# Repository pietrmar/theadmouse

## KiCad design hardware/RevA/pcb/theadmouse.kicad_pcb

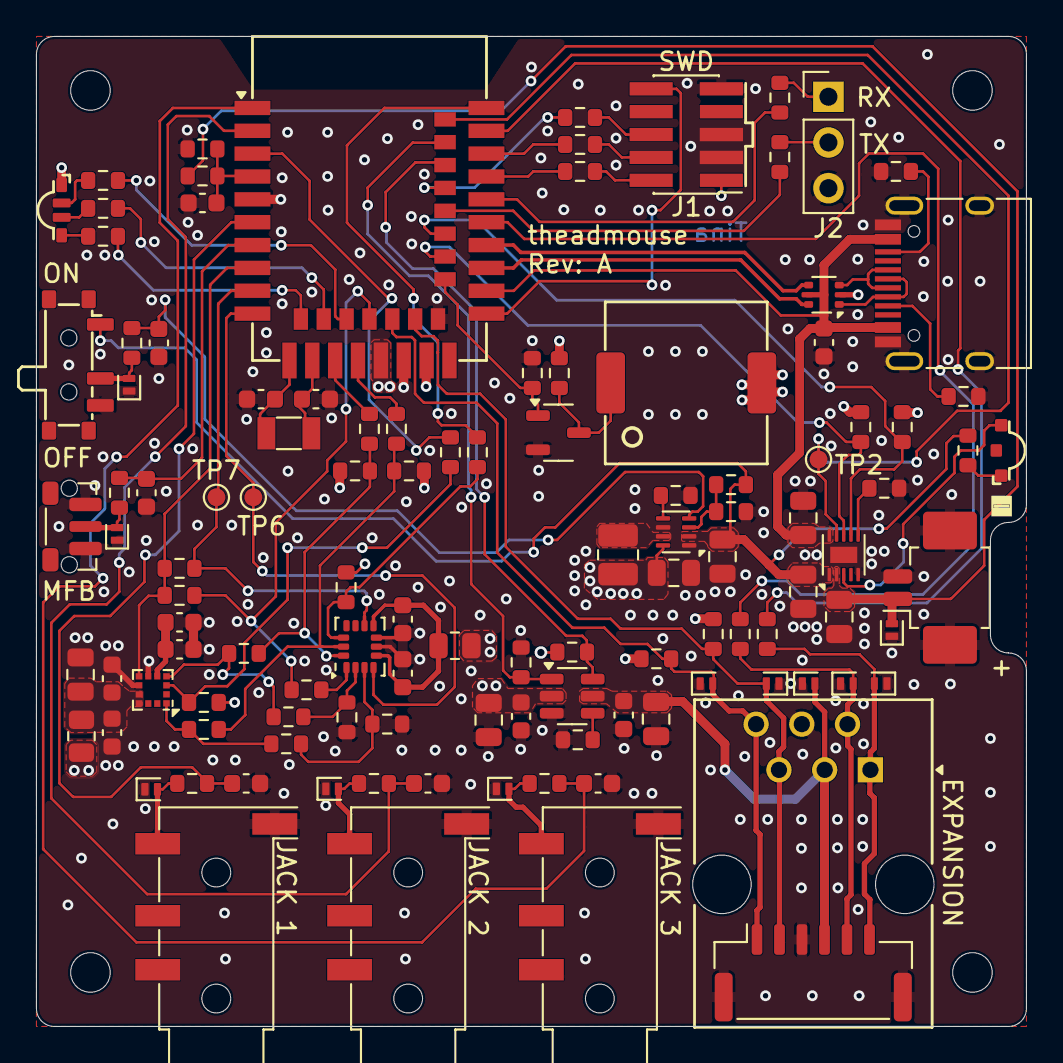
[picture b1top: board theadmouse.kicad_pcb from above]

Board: 4 copper layers, 55.0 x 55.0 mm, 119 parts (0 on the bottom side), 82 nets.

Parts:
C1, C2: 15p; C_0603_1608Metric
C3, C8, C11, C13, C14, C15, C16, C17, C19, C26: 100n; C_0603_1608Metric
C4, C5, C6, C9, C10, C12, C18, C25: 10u; C_0805_2012Metric
C7, C21, C22, C23, C24: 10n; C_0603_1608Metric
D1, D2, D3, D4, D5, D6, D7, D8, D9, D10, D12: H5VL10B; D_SOD-882
D11: LED_STATUS; LED_RGB_TUOZHAN_P4-1204RGBWS2-1.5T-A_Horizontal
D13: LED_PGOOD; LED_Green_MEIHUA_MHS110UGCT_Horizontal
H1, H2, H3, H4: MountingHole; MountingHole_2.2mm_M2_ISO7380
J1: CON_SWD; PinHeader_2x05_P1.27mm_Vertical_SMD
J2: CON_UART; PinHeader_1x03_P2.54mm_Vertical
J4: TYPE-C-31-M-12; USB_C_Receptacle_HRO_TYPE-C-31-M-12_Custom3D
J5: CON_BAT; Molex_PicoBlade_53261-0271_1x02-1MP_P1.25mm_Horizontal
J6: CON_EXT; JST_GH_SM06B-GHS-TB_1x06-1MP_P1.25mm_Horizontal
J7: CON_EXT_RJ; RJ25_TE_215876-1_Horizontal
J8, J9, J10: PJ-320D-4A; Jack_3.5mm_KoreanHropartsElec_PJ-320D-4A_Horizontal_Custom
L1: 2u2; L_1008_2520Metric
LS1: FUET-9018; Buzzer_FUET_FST-9018_9x9mm
Q1: HL2312; SOT-23-3
R1, R2, R3, R4, R5, R6, R21, R30: 10k; R_0603_1608Metric
R7, R8, R11, R12, R41, R44, R45, R49: 100R; R_0603_1608Metric
R9, R10, R13, R14, R16, R17, R18, R53: 22R; R_0603_1608Metric
R19, R20: 5k1; R_0603_1608Metric
R22: 4M02; R_0603_1608Metric
R23: 10M; R_0603_1608Metric
R24, R26, R32, R34, R35, R36, R37, R38, R39, R40: 0R; R_0603_1608Metric
R25, R43: 100k; R_0603_1608Metric
R27: 4k3; R_0603_1608Metric
R28: 267k; R_0603_1608Metric
R29, R50, R51: 470k; R_0603_1608Metric
R31, R33: 0R; R_0805_2012Metric
R42: 1k; R_0603_1608Metric
R46: 470R; R_0603_1608Metric
R47: 390R; R_0603_1608Metric
R48: 270R; R_0603_1608Metric
R52: 1k5; R_0603_1608Metric
SW1: SW_PWR; SW_SPDT_ALPS_SSSS811101_SMT_Horizontal
SW2: SW_MFB; SW_Push_1P1T-MP_NO_Horizontal_Alps_SKRTLAE010_Custom3D
TP2: ~{CHRG_INT}; TestPoint_Pad_D1.0mm
TP6: SENS_IMU_INT1; TestPoint_Pad_D1.0mm
TP7: SENS_IMU_INT2; TestPoint_Pad_D1.0mm
U1: E73-2G4M08S1C; Module_RF_Ebyte_E73-2G4M08S1C_Castellated
U2: USBLC6-2P6; SOT-666
U3: BQ25186; Texas_DLH0010A_WSON-10-1EP_2.2x2mm_P0.4mm_EP0.9x1.5mm
U4: TPS22950; SOT-23-6
U5: TPS62840DLC; Texas_VSON-HR-8_1.5x2mm_P0.5mm
U6: LSM6DSL; LGA-14_3x2.5mm_P0.5mm_LayoutBorder3x4y
U7: LIS2MDL; LGA-12_2x2mm_P0.5mm
Y1: 32.768 kHz; Crystal_SMD_3215-2Pin_3.2x1.5mm

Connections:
/BTN_JACK_1: C21.2, R41.1, U1.6 (P1.13)
/BTN_JACK_2: C22.2, R44.1, U1.2 (P1.10)
/BTN_JACK_3: C23.2, R45.1, U1.1 (P1.11)
/BTN_MFB: C24.2, R49.1, U1.7 (P0.02/AIN0)
/CHRG_I2C_SCL: R1.2, U1.30 (P0.17), U3.8 (SCL)
/CHRG_I2C_SDA: R2.2, U1.32 (P0.20), U3.7 (SDA)
/EXT_3V3_EN: R29.1, U1.40 (P1.04), U4.1 (ON)
/EXT_GPIO_1: D4.2 (A2), J6.5 (Pin_2), J7.2, R11.2
/EXT_GPIO_2: D3.2 (A2), J6.6 (Pin_1), J7.1, R12.1
/EXT_I2C_SCL: D7.2 (A2), J6.1 (Pin_6), J7.6, R5.2, U1.20 (P0.12)
/EXT_I2C_SDA: D6.2 (A2), J6.2 (Pin_5), J7.5, R6.2, U1.22 (P0.07)
/LED_B: R48.2, U1.16 (P0.08)
/LED_G: R47.2, U1.14 (P0.06)
/LED_R: R46.2, U1.12 (P0.26)
/Power/~CHRG_PG: D13.1 (K), U3.3 (~PG/GPO)
/SENS_IMU_INT_1: TP6.1, U1.10 (P0.30/AIN6), U6.4 (INT1)
/SENS_IMU_INT_2: R32.2, TP7.1, U1.9 (P0.31/AIN7), U6.9 (INT2)
/SENS_MAG_DRDY: R32.1, R40.2, U1.8 (P0.29/AIN5), U7.7 (DRDY)
/SENS_SPI_MISO: R40.1, R53.2, U1.18 (P0.04/AIN2)
/SENS_SPI_MOSI: R4.2, R13.1, R39.2, U6.14 (SDA)
/SENS_SPI_SCLK: R3.2, R14.1, R38.2, U6.13 (SCL)
/SPK_PWM: Q1.1 (G), R43.2, U1.28 (P0.15)
/SWCLK: J1.4, R10.2
/SWDIO: J1.2, R9.1
/SWO: J1.6, R16.2
/UART_RX: J2.1, R8.1
/UART_TX: J2.2, R7.2
/USB_D+: U1.31 (DP), U2.4 (I/O2)
/USB_D-: U1.29 (DM), U2.6 (I/O1)
/VBAT_MEAS: C7.1, R22.2, R23.1, U1.4 (P0.28/AIN4)
/~CHRG_INT: TP2.1, U1.42 (P1.06), U3.9 (~INT)
/~EXT_3V3_FAULT: R25.2, U1.38 (P1.02), U4.6 (~FLT)
/~RESET: J1.10, U1.26 (P0.18/RESET)
/~SENS_IMU_CS: R17.1, R50.2, U6.12 (CS)
/~SENS_MAG_CS: R18.2, R51.2, U7.3 (~CS)
EXT_3V3: C8.1, C9.1, D5.2 (A2), J6.4 (Pin_3), J7.3, U4.5 (VOUT)
GND: C1.2, C2.2, C3.2, C4.2, C5.2, C6.2, C7.2, C8.2, C9.2, C10.2, C11.2, C12.2, C13.2, C14.2, C15.2, C16.2, C17.2, C18.2, C19.2, C21.1, C22.1, C23.1, C24.1, C25.2, C26.2, D1.1 (A1), D2.1 (A1), D3.1 (A1), D4.1 (A1), D5.1 (A1), D6.1 (A1), D7.1 (A1), D8.1 (A1), D9.1 (A1), D10.1 (A1), D12.1 (A1), J1.3, J1.5, J1.9, J2.3, J4.A1 (GND), J4.A12 (GND), J4.B1 (GND), J4.B12 (GND), J4.S1 (SHIELD), J5.2, J5.MP (MountPin), J6.3 (Pin_4), J6.MP (MountPin), J7.4, J8.G, J9.G, J10.G, Q1.2 (S), R19.2, R20.2, R21.1, R23.2, R26.1, R27.2, R28.1, R29.2, R36.1, R37.2, R43.1, SW1.3 (A), SW2.1, U1.5 (GND@1), U1.21 (GND@2), U1.24 (GND@3), U2.2 (GND), U3.5 (GND), U3.11 (THERMAL), U4.3 (GND), U5.1 (GND), U5.6 (STOP), U6.6 (GND), U6.7 (GND), U7.6 (GND), U7.8 (GND)
unnamed: D2.2 (A2), R30.1, SW1.2 (B)
unnamed: D8.2 (A2), J8.T, R41.2
unnamed: D9.2 (A2), J9.T, R44.2
unnamed: D10.2 (A2), J10.T, R45.2
unnamed: D11.2 (BK), R48.1
unnamed: D11.1 (GK), R47.1
unnamed: D11.3 (RK), R46.1
unnamed: D12.2 (A2), R49.2, SW2.2
unnamed: D13.2 (A), R52.1
unnamed: J4.A5 (CC1), R20.1
unnamed: J4.B5 (CC2), R19.1
unnamed: J4.A6 (D+), J4.B6 (D+), U2.3 (I/O2)
unnamed: J4.A7 (D-), J4.B7 (D-), U2.1 (I/O1)
unnamed: LS1.2, Q1.3 (D), R42.1
unnamed: R10.1, U1.39 (SWDCLK)
unnamed: R9.2, U1.37 (SWDIO)
unnamed: C1.1, U1.11 (P0.00/XL1), Y1.2
unnamed: C2.1, U1.13 (P0.01/XL2), Y1.1
unnamed: R18.1, U1.3 (P0.03/AIN1)
unnamed: R13.2, U1.15 (P0.05/AIN3)
unnamed: R12.2, U1.41 (P0.09/NFC1)
unnamed: R17.2, U1.43 (P0.10/NFC2)
unnamed: R11.1, U1.33 (P0.13)
unnamed: R7.1, U1.34 (P0.22)
unnamed: R8.2, U1.35 (P0.24)
unnamed: R16.1, U1.36 (P1.00)
unnamed: R14.2, U1.17 (P1.09)
unnamed: R21.2, U3.6 (TS/MR)
unnamed: R27.1, U4.4 (ILIM)
unnamed: C13.1, R30.2, U5.4 (EN)
unnamed: R24.1, R26.2, U5.3 (MODE)
unnamed: L1.1, U5.7 (SW)
unnamed: R28.2, U5.5 (VSET)
unnamed: R35.1, R36.2, U6.3 (SCX)
unnamed: R53.1, U6.1 (SDO/SA0)
unnamed: R34.2, R37.1, U6.2 (SDX)
unnamed: C14.1, C15.1, R31.1, U6.5 (VDDIO), U6.8 (VDD)
unnamed: C19.1, C26.1, U7.5 (C1)
unnamed: R35.2, R38.1, U7.1 (SCL/SPC)
unnamed: R34.1, R39.1, U7.4 (SDA/SDI/SDO)
unnamed: C16.1, C17.1, C18.1, R33.1, U7.9 (Vdd), U7.10 (Vdd_IO)
VBAT: C6.1, D1.2 (A2), J5.1, R22.1, U3.2 (BAT)
VBUS: C3.1, C4.1, J4.A4 (VBUS), J4.A9 (VBUS), J4.B4 (VBUS), J4.B9 (VBUS), U1.27 (VBUS), U2.5 (VBUS), U3.10 (IN)
VDD_3V3: C10.1, C11.1, C25.1, D11.4 (A), J1.1, L1.2, LS1.1, R1.1, R2.1, R3.1, R4.1, R5.1, R6.1, R25.1, R31.2, R33.2, R42.2, R50.1, R51.1, U1.19 (VDD), U1.23 (VDDH), U4.2 (VIN), U5.8 (VOS)
VSYS: C5.1, C12.1, R24.2, R52.2, SW1.1 (C), U3.1 (SYS), U5.2 (VIN)

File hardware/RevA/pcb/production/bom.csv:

Designator,Footprint,Quantity,Value,LCSC Part #
"C1, C2",0603,2,15p,C1644
"C10, C12, C18, C25, C4, C5, C6, C9",0805,8,10u,C15850
"C11, C13, C14, C15, C16, C17, C19, C26, C3, C8",0603,10,100n,C2762593
"C21, C22, C23, C24, C7",0603,5,10n,C85973
"D1, D10, D12, D2, D3, D4, D5, D6, D7, D8, D9",D_SOD-882,11,H5VL10B,C7420372
D11,LED_RGB_TUOZHAN_P4-1204RGBWS2-1.5T-A_Horizontal,1,LED_STATUS,C2827295
D13,LED_Green_MEIHUA_MHS110UGCT_Horizontal,1,LED_PGOOD,C404269
J1,PinHeader_2x05_P1.27mm_Vertical_SMD,1,CON_SWD,C41376037
"J10, J8, J9",Jack_3.5mm_KoreanHropartsElec_PJ-320D-4A_Horizontal_Custom,3,PJ-320D-4A,C95562
J4,USB_C_Receptacle_HRO_TYPE-C-31-M-12_Custom3D,1,TYPE-C-31-M-12,C165948
J5,Molex_PicoBlade_53261-0271_1x02-1MP_P1.25mm_Horizontal,1,CON_BAT,C177225
J6,JST_GH_SM06B-GHS-TB_1x06-1MP_P1.25mm_Horizontal,1,CON_EXT,C133065
L1,1008,1,2u2,C2043106
LS1,Buzzer_FUET_FST-9018_9x9mm,1,FUET-9018,C391035
Q1,SOT-23-3,1,HL2312,C28646272
"R1, R2, R21, R30, R5, R6",0603,6,10k,
"R10, R13, R14, R16, R17, R18, R53, R9",0603,8,22R,
"R11, R12, R41, R44, R45, R49, R7, R8",0603,8,100R,
"R19, R20",0603,2,5k1,
R22,0603,1,4M02,C322160
R23,0603,1,10M,
"R25, R43",0603,2,100k,
"R26, R36, R37, R38, R39",0603,5,0R,
R27,0603,1,4k3,
R28,0603,1,267k,
"R31, R33",0805,2,0R,
R42,0603,1,1k,
R46,0603,1,470R,
R47,0603,1,390R,
R48,0603,1,270R,
"R50, R51",0603,2,470k,
R52,0603,1,1k5,
SW1,SW_SPDT_ALPS_SSSS811101_SMT_Horizontal,1,SW_PWR,C109335
SW2,SW_Push_1P1T-MP_NO_Horizontal_Alps_SKRTLAE010_Custom3D,1,SW_MFB,C110293
U1,Module_RF_Ebyte_E73-2G4M08S1C_Castellated,1,E73-2G4M08S1C,C356849
U2,SOT-666,1,USBLC6-2P6,C15999
U3,Texas_DLH0010A_WSON-10-1EP_2.2x2mm_P0.4mm_EP0.9x1.5mm,1,BQ25186,C44639442
U4,SOT-23-6,1,TPS22950,C7587833
U5,Texas_VSON-HR-8_1.5x2mm_P0.5mm,1,TPS62840DLC,C2071859
U6,LGA-14_3x2.5mm_P0.5mm_LayoutBorder3x4y,1,LSM6DSL,C126672
U7,LGA-12_2x2mm_P0.5mm,1,LIS2MDL,C919695
Y1,Crystal_SMD_3215-2Pin_3.2x1.5mm,1,32.768 kHz,C32346

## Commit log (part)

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2025-02-27 initial commit of firmware directory
2025-02-27 firmware: basic logging setup
2025-03-22 firmware: empty app.overlay and slim down prj.conf for usage with the xiao_ble/nrf52840/sense
    The "xiao_ble/nrf52840/sense" already should have everything configured
    correctly for us.
2025-04-12 firmware: main.c: add `dfureboot` command
2025-04-13 firmware: first simple HID over GATT (HOG) support
    This is mostly based on the example provided by Zephyr.
2025-04-13 firmware: hog.c: use static GATT service definition again
2025-04-13 firmware: prj.conf: remove support for dynamic GATT service configuration
2025-04-13 firmware: main.c: read sensor data and pass send it out over HOG
2025-04-15 firmware: drivers: add custom lsm6dsl driver from the v3.7.99-ncs2 source tree
2025-04-15 firmware: drivers: lsm6dsl: set custom thread name on own trigger thread
2025-05-06 firmware: main.c: first proof of concept
2025-06-29 firmware: main.c: add comment
2025-08-09 hardware: RevA: create production output for JLCPCB
    These files were used to place the RevA order at JLCPCB.
2025-08-12 firmware: main.c: generate a friendly device name from the unique device ID
2025-08-14 firmware: add boilerplate code for the theadmouse board
2025-08-21 firmware: boards: theadmouse: initial board bringup
    Configures the following:
    - PWM for the RGB LED and the piezo buzzer
    - SPI in 4-wire mode (needs R40 stuffed on RevA)
    - LSM6DSL IMU
    - LIS2MDL Magnetometer
    - UART
2025-08-21 firmware: remove custom lsm6dsl driver for now
    I will take a detailed look at this later, but for now the demo is working
    with the driver from Zephyr unmodified.
2025-09-22 scripts: debug.sh: add `--enable-tpwr` flag
2025-10-15 firmware: boards: theadmouse: enable LIS2MDL runtime ODR setting
2025-10-16 firmware: main.c: first implementation of reading the magnetometer
    Just for a quick test, however it does not work fully yet.
2025-10-16 firmware: prj.conf: add CONFIG_UART_LINE_CTRL=y
2025-10-24 firmware: main.c: add telemetry first basic output for debugging
2025-10-24 WIP: firmware: theadmouse: implement forwarding beacons as HID packets
    This is very ugly and only a quick proof of concept, but it works, although
    pretty rough and low update rate.
2025-10-29 WIP: firmware: puckjs: implement periodic advertising
2025-10-29 WIP: firmware: theadmouse: parse target BT address from string
2025-11-03 firmware: boards: theadmouse: configure 0x1209:0x7EAD VID:PID for USB
    The VID and PID pair was requested from pid.codes in the following
    (currently pending) pull request:
    - https://github.com/pidcodes/pidcodes.github.com/pull/1112
2025-11-06 firmware: telemetry_uart: make the write call serialized
    This will prevent interleaved output in case there are multiple writers and
    the ringbuffer became full so that only a partial write was done.
2025-11-06 firmware: boards: theadmouse: set `mpi-cmd-uart` chosen node
2025-11-07 firmware: change USB device product name to TheadMouse
2025-11-07 firmware: at_cmd: add new `at_dispatch_cmd()` helper
    This will allow us to trigger commands without needing to go through the
    parsing step.
2025-11-07 firmware: at_cmd: make necessary types and helpers public needed for `at_dispatch_cmd()`
2025-11-07 firmware: at_cmd: first basic implementation of MX/MY commands
    For a quick proof of concept we can just use `hog_push_report()` directly
    but we will need a proper queueing system in place later.
2025-11-08 firmware: cmd_uart: don't pass len to `at_handle_line()` and use `AT_LINE_MAX` macro
2025-11-08 firmware: boards: theadmouse: add the GPIO buttons
2025-11-08 firmware: add button_manager
    This just takes button presses (or later other inputs) and dispatches AT
    commands from a table. Simple but works.
    The buttons can be defined in the device-tree.
2025-11-08 firmware: prj.conf: enable the input subsystem and the GPIO input key driver
2025-11-08 firmware: at_cmd: add first basic implementation of `AT BM <button>`
    These should be implemented cleaner, see the comments that were added.
2025-11-11 firmware: prj.conf: enable LittleFS filesystem
2025-11-12 firmware: at_cmd: reworkt the API a bit
    - Separate the parsing step into a `at_parse_line_[inplace|copy]()` function
    - Provide `*_inplace()` and `*_copy()` variants for parsing and handling
    - Add flags for parsing, for exampel to allow executing commands without the
    AT prefix
2025-11-12 firmware: main: disable `wipenvs` command for now
2025-11-13 firmware: at_cmd: minor log message change about "param type"
2025-11-13 firmware: button_manager: add new functions
    - Fix parameters in `button_manager_set_mapping()`
    - Add `button_manager_get_mapping()`
    - Add `button_manager_get_num_buttons()`
2025-11-13 firmware: main: call `slot_manager_init()`
2025-11-13 firmware: at_cmd: add TODO comment about possibly interleaving AT print functions
2025-11-13 firmware: at_cmd: make `at_param_get_str()` parameters const
2025-11-13 firmware: at_cmd: implement slot management commands and color command
2025-11-15 firmware: button_manager: add TODO comment about using callbacks
2025-11-15 firmware: button_manager: use new AT command queue
2025-11-17 firmware: at_cmd: make sure commands are dispatched only from the AT command thread
2025-11-17 firmware: slot_manager: load slot 0 by enqueueing it on the AT command queue
    This will ensure that the initial slot loading happens from the correct
    thread.
2025-11-18 firmware: at_cmd: implement `at_cmd_enqueue_and_wait_*()` functions
    Currently we only support K_FOREVER for the timeout for now, otherwise
    we would need to slab allocate the `result_ptr` and `done_sem` and use
    some reference counting.
2025-11-18 firmware: main: wait for AT command to finish and print error code
2025-11-18 firmware: slot_manager: drop `cmd == NULL` check
2025-11-19 firmware: add `input_protocol.h` header
    This will be mostly used to have hold common defines from the FABI/FLipMouse
    ecosystem.
    For now we only have the input mode.
2025-11-19 firmware: cmd_uart: remove mutex for `cmd_uart_write()`
    This is not needed, the caller to `cmd_uart_write()` should ensure that
    no concurrent writes happen otherwise the output will be interleaved.
2025-11-19 firmware: cmd_uart: add TODO comment about better receive line handling
2025-11-19 firmware: add headmouse_input module
    This creates two virtual input devices that can be used to push events
    which then will be sent using HID over GATT.
2025-11-19 firmware: at_cmd: MM: use `hm_input_report_rel()` now
    This will now correctly push the event into the input device, so we can
    handle it properly.
2025-11-19 firmware: remove IMU/MAG related things for now
    We will do this later correctly after we cleanly implemented HID over GATT
    and such.
2025-11-19 firmware: main: fix deprecation warning for `BT_LE_ADV_CONN`
2025-11-19 firmware: prj.conf: enable CONFIG_BT_HIDS
2025-11-25 firmware: main: sort includes and add TODO about BLE use-cases
2025-11-25 firmware: main: re-start advertising when disconnected
2025-11-26 firmware: prj.conf: use custom LSM6DSL driver
2025-11-29 firmware: prj.conf: use custom LIS2MDL driver
2025-12-02 firmware: re-add MadgwickAHRS library for now
    Downloaded from:
    https://x-io.co.uk/downloads/madgwick_algorithm_c.zip
2025-12-02 firmware: boards: theadmouse: use lis2mdl for `mpi,mag` chosen node
2025-12-02 firmware: prj.conf: enable LSM6DSL temperature readout
2025-12-03 firmware: telemetry_uart: make `telemetry_uart_write()` non-static
2026-01-14 firmware: at_cmd: clamp WA command at 1000 ms and print a warning
2026-01-20 firmware: button_manager: add `button_manager_get_button_state_string()` function
    This reports the current state of all buttons as a string of 1 and 0.
2026-01-20 firmware: at_cmd: include button states in periodic reporting
2026-01-20 firmware: at_cmd_param: change at_cmd_param_[clone|free]() API
    This changes the behavior assuming that the caller has already allocated
    the struct and this only handles the "deep" copy aspect, which currently
    is the case for a heap allocated string.
2026-01-21 firmware: at_cmd: make use of the new common `enum axis` enum
2026-01-21 firmware: at_cmd: include the absolute HID position in the report
2026-01-21 firmware: slot_manager: serialize sensitivity as AX, AY commands on save
2026-01-21 firmware: hm_hid_evt: use Zephyr USB HID header for HID_KEY_* codes
2026-01-21 firmware: at_cmd: format the `at_cmds[]` table consistently
2026-01-21 firmware: keymaps: adjust to our codebase and include in the build
2026-01-21 firmware: at_cmd: add KL command to get/set the keyboard layout
2026-01-21 firmware: at_cmd: more consistent error message for the KL command
2026-01-22 firmware: at_cmd: ID: report ForceSensor=IMU
2026-01-22 firmware: slot_manager: remove old input mode setting as it was moved to the motion_engine
2026-01-22 firmware: common.h: use explicit values for AXIS_X and AXIS_Y
2026-01-23 firmware: at_cmd_param: make the param flags into an enum
2026-01-23 firmware: main: use the new `AT_PARSER_FLAG_ALLOW_NO_PREFIX` flag
2026-01-23 firmware: slot_manager: serialize DX, DY values on save
2026-01-23 firmware: headmouse_input: add functions for handling KEY_* and KEYPAD_* strings
    The KEY_*/KEYPAD_* string key-codes are stored in an internal/intermediate
    code as a single uint8_t.
    Codes that are just ASCII characters will be mapped their own ASCII
    character. This allows us to make keyboard layout look-ups.
    Modifier keys are mapped into the ASCII range 0x10 - 0x17 which contains
    some unused ASCII control characters.
2026-01-23 firmware: at_cmd: add parsing and serializing of AT_CMD_PARAM_TYPE_KEYS
    Also print the partial string on error for better debugging purposes.
2026-01-23 firmware: at_cmd: add a new flag AT_CMD_FLAG_HOLD
    When this flag is set it is possible to pass an AT command code in the
    ctx that will be enqueue (with the same parameters) by the button manager
    when the button is released.
    This is not the cleanest architecture, but for now it'll do.
2026-01-23 firmware: button_manager: add input key-codes for UP, DOWN, LEFT and RIGHT
2026-01-24 firmware: dts: bindings: add pwm-spk binding definition
2026-01-24 firmware: ble_hid_service: drop inner loop inside ble_hid_thread()
    Since we do not do any coalescing this is not necessary and does not give
    us anything.
    In the future we could coalesce at least mouse movements, but this has
    some edge cases, so let's not do that for now.
2026-01-27 firmware: make the telemetry optional using CONFIG_TELEMETRY Kconfig options
2026-04-30 firmware: prj.conf: enable power management
2026-04-30 firmware: add first version of app_power_manager module
2026-04-30 scripts: flash.sh run detach command before quit
    This prevents an extra print about the remote target still being active and
    seems cleaner to me.
2026-05-08 firmware: button_manager: report activity on button presses
2026-05-08 firmware: ble_hid_service: allow calling `ble_hid_service_init()` multiple times
2026-05-08 firmware: ble: make `ble_start_adv()` static
2026-05-08 firmware: app_power_manager: suspend/resume the BLE module
2026-05-08 firmware: prj.conf: set app_power_manager log-level to debug
2026-06-16 firmware: ble: add TODO comments about disconnecting on suspend
2026-06-16 firmware: slot_manager: rename `slot_manager_play_note()` to `_play_tone()`
    This is a bit more accurate.
2026-06-16 firmware: slot_manager: implement `slot_manager_set_rgb_led_color()`
2026-06-16 firmware: boards: theadmouse: use new device-tree bindings for the PWM RGB LED
